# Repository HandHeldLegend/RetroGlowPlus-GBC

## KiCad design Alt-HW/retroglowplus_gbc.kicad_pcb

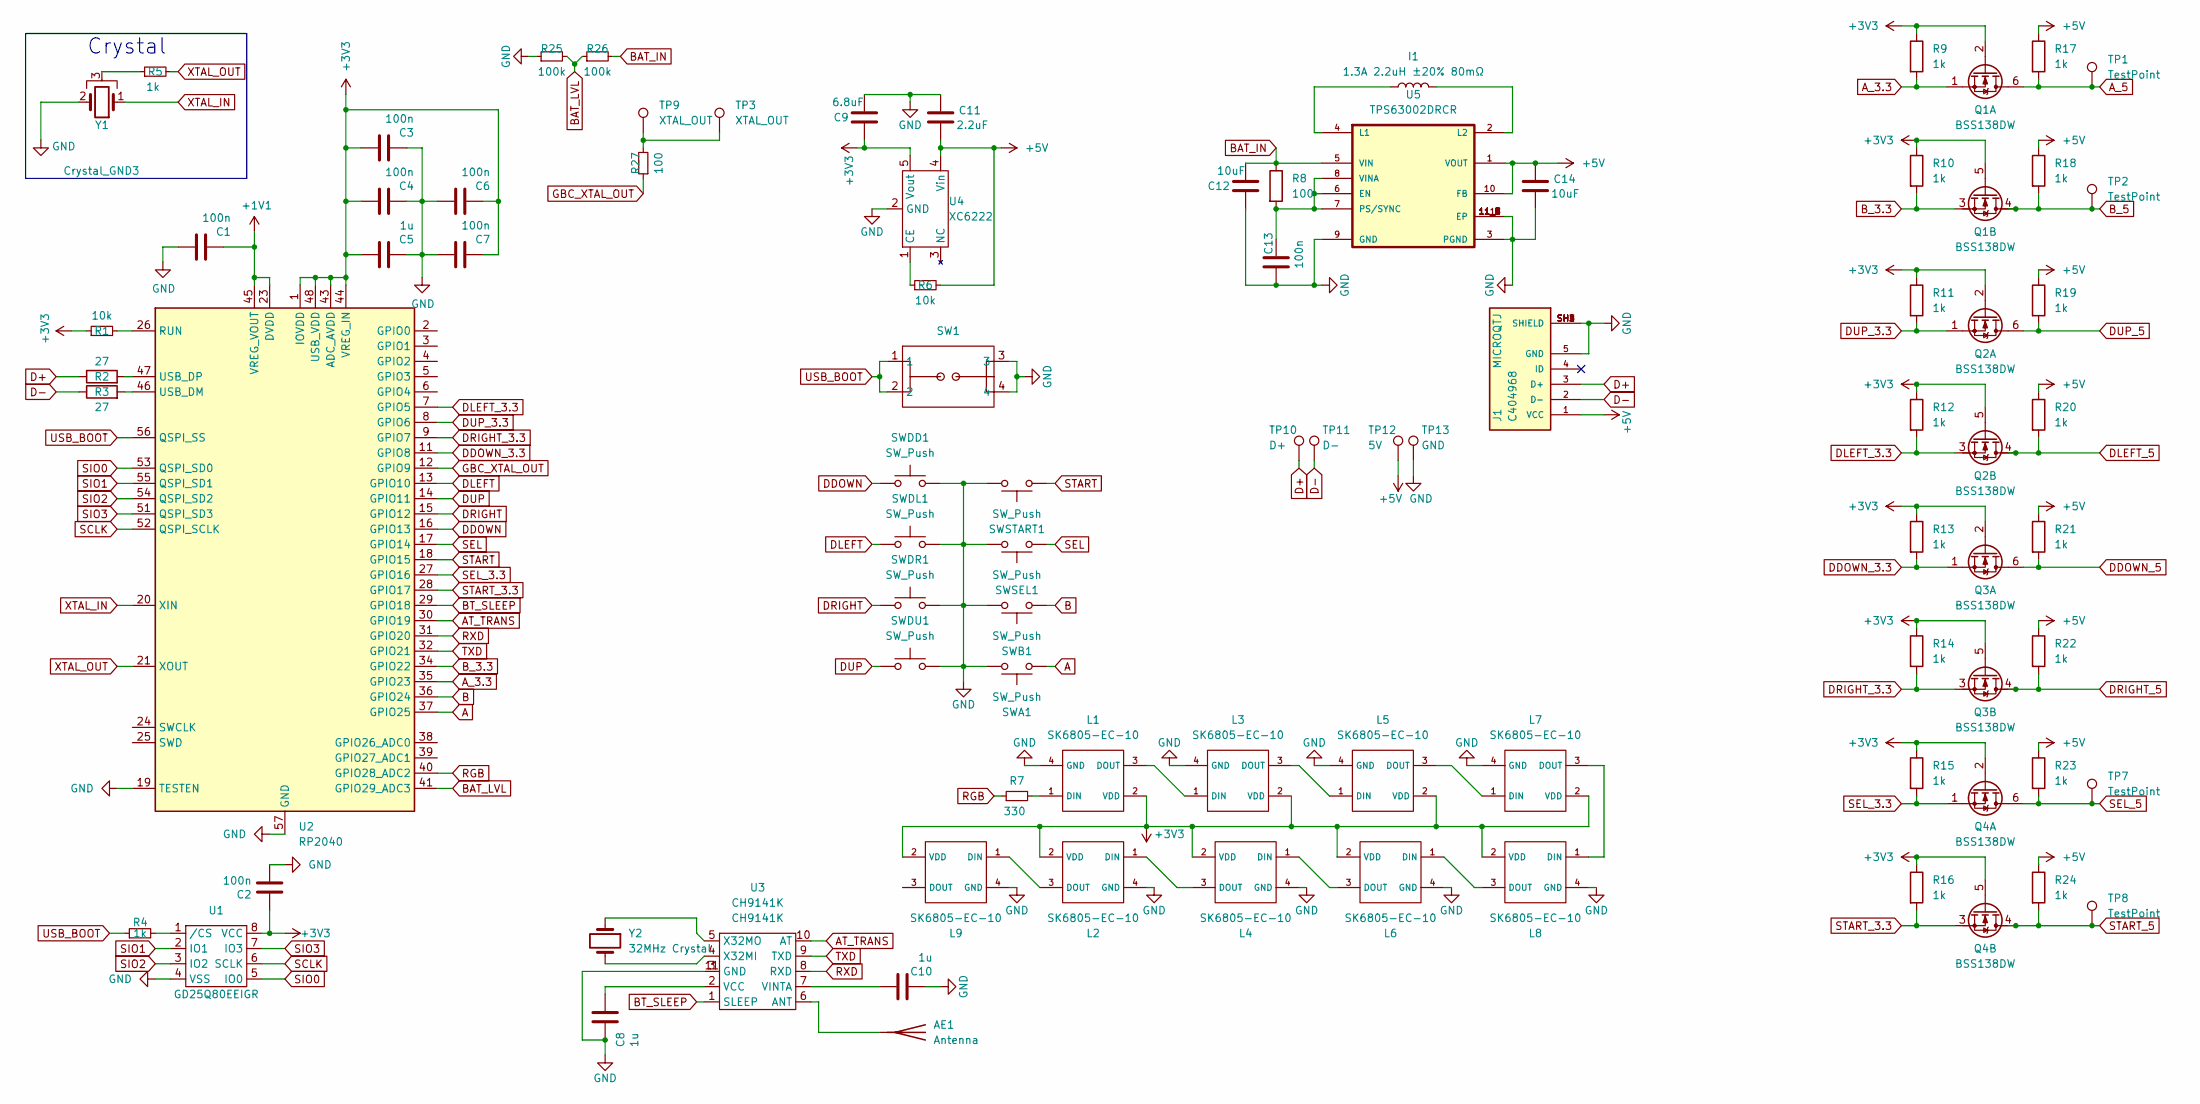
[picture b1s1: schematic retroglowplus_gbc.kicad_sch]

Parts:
AE1: Antenna; L_1206_3216Metric; MPN 2450AT18A100E
C1, C3, C4, C6, C7: 100n; C_0402_1005Metric
C2, C13: 100n; C_0201_0603Metric
C5, C8, C10: 1u; C_0402_1005Metric
C9: 6.8uF; C_0603_1608Metric
C11: 2.2uF; C_0603_1608Metric
C12, C14: 10uF; C_0805_2012Metric
I1: 1.3A 2.2uH ±20% 80mΩ; L_1008_2520Metric; MPN MIP25202R2MBE; LCSC C315721
J1: MICROQTJ; SHOUHAN_MICROQTJ; PARTREV A/0; LCSC C404968
L1, L2, L3, L4, L5, L6, L7, L8, L9: SK6805-EC-10
Q1, Q2, Q3, Q4: BSS138DW; SOT-363_SC-70-6; MPN BSS138DW-7-F; LCSC C154900
R1, R6: 10k; R_0201_0603Metric
R2, R3: 27; R_0201_0603Metric
R4, R5, R9, R10, R11, R12, R13, R14, R15, R16, R17, R18, R19, R20, R21, R22, R23, R24: 1k; R_0201_0603Metric
R7: 330; R_0201_0603Metric
R8, R27: 100; R_0201_0603Metric
R25, R26: 100k; R_0201_0603Metric
SW1: 1TS026A-1000-0550; MPN 1TS026A-1000-0550; LCSC C913778
SWA1: SW_Push; ring_pad_small
SWB1: SW_Push; ring_pad_small
SWDD1: SW_Push; ring_dpad
SWDL1: SW_Push; ring_dpad
SWDR1: SW_Push; ring_dpad
SWDU1: SW_Push; ring_dpad
SWSEL1: SW_Push; GBC_Start_Select
SWSTART1: SW_Push; GBC_Start_Select
TP1, TP2, TP7, TP8: TestPoint; TestPoint_Pad_2.5x2.5mm
TP3, TP9: XTAL_OUT; TestPoint_Pad_2.5x2.5mm
TP10: D+; TestPoint_Pad_2.5x2.5mm
TP11: D-; TestPoint_Pad_2.5x2.5mm
TP12: 5V; TestPoint_Pad_2.5x2.5mm
TP13: GND; TestPoint_Pad_2.5x2.5mm
U1: GD25Q80EEIGR; USON-8-EP(2x3); MPN GD25Q80EEIGR; LCSC C2874937
U2: RP2040; QFN-56-1EP_7x7mm_P0.4mm_EP3.2x3.2mm
U3: CH9141K; ESSOP-10; MPN CH9141K
U4: XC6222; SOT-89-5; MPN XC6222B331PR-G
U5: TPS63002DRCR; VREG_V62_16624-01YE; MPN TPS63002DRCR
Y1: Crystal_GND3; Resonator_SMD_Murata_CSTxExxV-3Pin_3.0x1.1mm; MPN CSTNE12M0GH5L000R0
Y2: 32MHz Crystal; Oscillator_SMD_EuroQuartz_XO32-4Pin_3.2x2.5mm; MPN CF4032M00012T5074007

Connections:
+1V1: C1.2, U2.23 (DVDD), U2.45 (VREG_VOUT), U2.50 (DVDD)
+3V3: C2.1, C3.1, C4.1, C5.1, C6.2, C7.2, C9.1, L1.2 (VDD), L2.2 (VDD), L3.2 (VDD), L4.2 (VDD), L5.2 (VDD), L6.2 (VDD), L7.2 (VDD), L8.2 (VDD), L9.2 (VDD), Q1.2 (G1), Q1.5 (G2), Q2.2 (G1), Q2.5 (G2), Q3.2 (G1), Q3.5 (G2), Q4.2 (G1), Q4.5 (G2), R1.1, R9.1, R10.1, R11.1, R12.1, R13.1, R14.1, R15.1, R16.1, U1.8 (VCC), U2.1 (IOVDD), U2.10 (IOVDD), U2.22 (IOVDD), U2.33 (IOVDD), U2.42 (IOVDD), U2.43 (ADC_AVDD), U2.44 (VREG_IN), U2.48 (USB_VDD), U2.49 (IOVDD), U4.5 (Vout)
+5V: C11.2, C14.1, J1.1 (VCC), R6.2, R17.1, R18.1, R19.1, R20.1, R21.1, R22.1, R23.1, R24.1, TP12.1, U4.4 (Vin), U5.1 (VOUT), U5.10 (FB); also elsewhere on the board
A: SWA1.1, U2.37 (GPIO25)
AT_TRANS: U2.30 (GPIO19), U3.10 (AT)
A_3.3: Q1.1 (S1), R9.2, U2.35 (GPIO23)
A_5: Q1.6 (D1), R17.2, TP1.1
B: SWB1.1, U2.36 (GPIO24)
BAT_IN: C12.2, R8.1, R26.2, U5.5 (VIN); also elsewhere on the board
BAT_LVL: R25.2, R26.1, U2.41 (GPIO29_ADC3)
BT_SLEEP: U2.29 (GPIO18), U3.1 (SLEEP)
B_3.3: Q1.3 (D2), R10.2, U2.34 (GPIO22)
B_5: Q1.4 (S2), R18.2, TP2.1
D+: J1.3 (D+), R2.1, TP10.1
D-: J1.2 (D-), R3.1, TP11.1
DDOWN: SWDD1.1, U2.16 (GPIO13)
DDOWN_3.3: Q3.1 (S1), R13.2, U2.11 (GPIO8)
DDOWN_5: Q3.6 (D1), R21.2
DLEFT: SWDL1.1, U2.13 (GPIO10)
DLEFT_3.3: Q2.3 (D2), R12.2, U2.7 (GPIO5)
DLEFT_5: Q2.4 (S2), R20.2
DRIGHT: SWDR1.1, U2.15 (GPIO12)
DRIGHT_3.3: Q3.3 (D2), R14.2, U2.9 (GPIO7)
DRIGHT_5: Q3.4 (S2), R22.2
DUP: SWDU1.1, U2.14 (GPIO11)
DUP_3.3: Q2.1 (S1), R11.2, U2.8 (GPIO6)
DUP_5: Q2.6 (D1), R19.2
GBC_XTAL_OUT: R27.1, U2.12 (GPIO9)
GND: C1.1, C2.2, C3.2, C4.2, C5.2, C6.1, C7.1, C8.2, C9.2, C10.2, C11.1, C12.1, C13.1, C14.2, J1.5 (GND), J1.SH1 (SHIELD), J1.SH2 (SHIELD), J1.SH3 (SHIELD), J1.SH4 (SHIELD), L1.4 (GND), L2.4 (GND), L3.4 (GND), L4.4 (GND), L5.4 (GND), L6.4 (GND), L7.4 (GND), L8.4 (GND), L9.4 (GND), R25.1, SW1.3, SW1.4, SWA1.2, SWB1.2, SWDD1.2, SWDL1.2, SWDR1.2, SWDU1.2, SWSEL1.2, SWSTART1.2, TP13.1, U1.4 (VSS), U2.19 (TESTEN), U2.57 (GND), U3.3 (GND), U3.11 (GND), U4.2 (GND), U5.3 (PGND), U5.9 (GND), U5.11 (EP), U5.11_1 (EP), U5.11_2 (EP), U5.11_3 (EP), U5.11_4 (EP), U5.11_5 (EP), U5.11_6 (EP), U5.11_7 (EP), U5.11_8 (EP), Y1.2; also elsewhere on the board
unnamed: AE1.1 (A), U3.6 (ANT)
unnamed: L1.1 (DIN), R7.2
unnamed: L1.3 (DOUT), L3.1 (DIN)
unnamed: L2.1 (DIN), L4.3 (DOUT)
unnamed: L2.3 (DOUT), L9.1 (DIN)
unnamed: L3.3 (DOUT), L5.1 (DIN)
unnamed: L4.1 (DIN), L6.3 (DOUT)
unnamed: L5.3 (DOUT), L7.1 (DIN)
unnamed: L6.1 (DIN), L8.3 (DOUT)
unnamed: L7.3 (DOUT), L8.1 (DIN)
unnamed: R5.1, Y1.3
unnamed: R27.2, TP3.1, TP9.1
unnamed: R4.2, U1.1 (/CS)
unnamed: R1.2, U2.26 (RUN)
unnamed: R3.2, U2.46 (USB_DM)
unnamed: R2.2, U2.47 (USB_DP)
unnamed: C8.1, U3.2 (VCC)
unnamed: C10.1, U3.7 (VINTA)
unnamed: U3.4 (X32MI), Y2.2
unnamed: U3.5 (X32MO), Y2.1
unnamed: R6.1, U4.1 (CE)
unnamed: C13.2, R8.2, U5.6 (EN), U5.7 (PS/SYNC), U5.8 (VINA)
unnamed: I1.1, U5.4 (L1)
unnamed: I1.2, U5.2 (L2)
RGB: R7.1, U2.40 (GPIO28_ADC2)
RXD: U2.31 (GPIO20), U3.8 (RXD)
SCLK: U1.6 (SCLK), U2.52 (QSPI_SCLK)
SEL: SWSEL1.1, U2.17 (GPIO14)
SEL_3.3: Q4.1 (S1), R15.2, U2.27 (GPIO16)
SEL_5: Q4.6 (D1), R23.2, TP7.1
SIO0: U1.5 (IO0), U2.53 (QSPI_SD0)
SIO1: U1.2 (IO1), U2.55 (QSPI_SD1)
SIO2: U1.3 (IO2), U2.54 (QSPI_SD2)
SIO3: U1.7 (IO3), U2.51 (QSPI_SD3)
START: SWSTART1.1, U2.18 (GPIO15)
START_3.3: Q4.3 (D2), R16.2, U2.28 (GPIO17)
START_5: Q4.4 (S2), R24.2, TP8.1
TXD: U2.32 (GPIO21), U3.9 (TXD)
USB_BOOT: R4.1, SW1.1, SW1.2, U2.56 (QSPI_SS)
XTAL_IN: U2.20 (XIN), Y1.1
XTAL_OUT: R5.2, U2.21 (XOUT)

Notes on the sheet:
Crystal

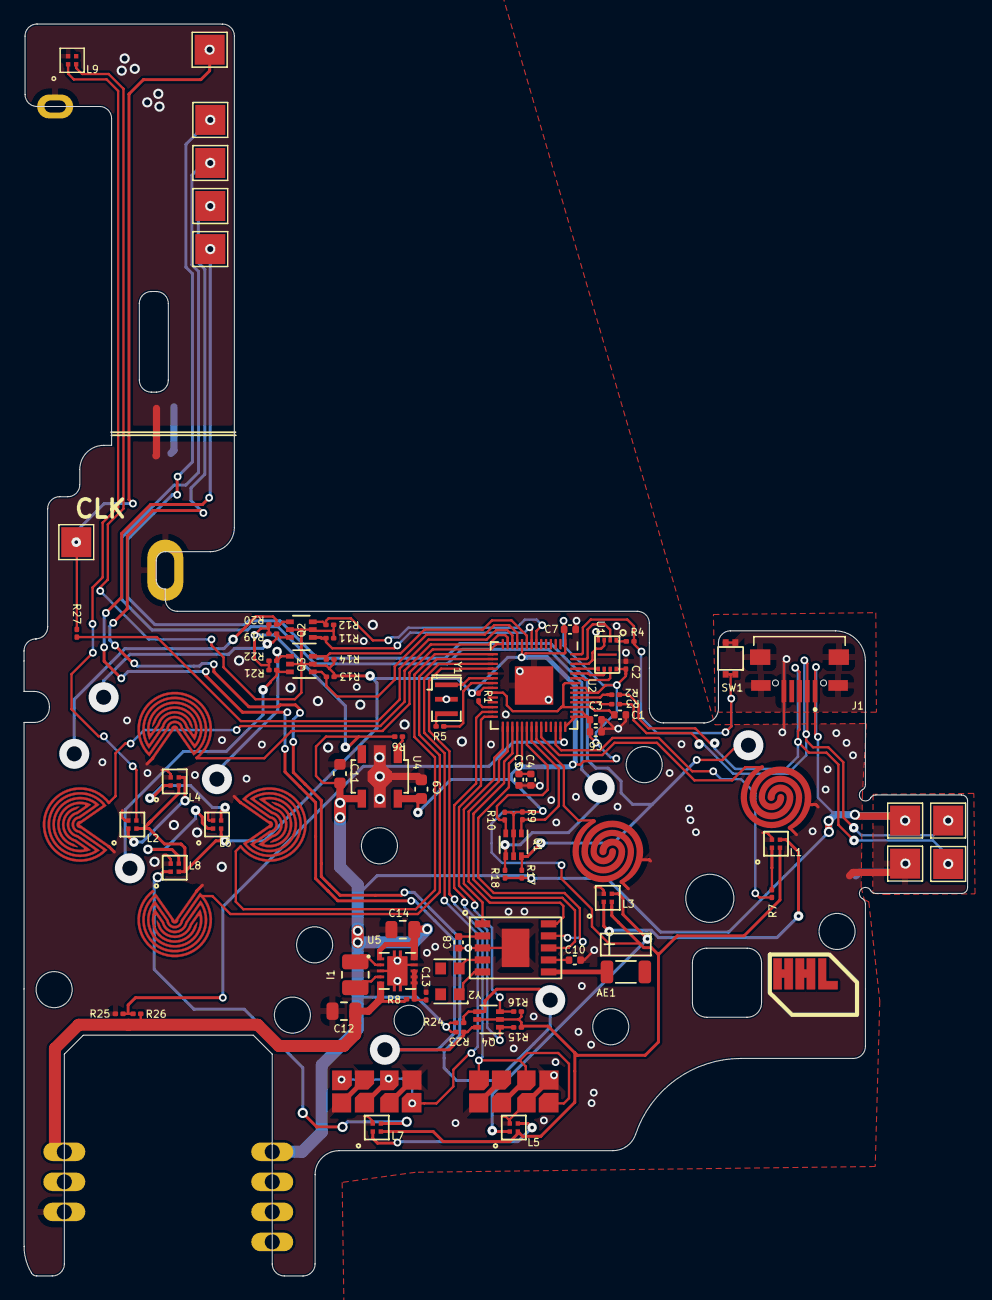
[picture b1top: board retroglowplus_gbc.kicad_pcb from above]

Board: 2 copper layers, 78.5 x 104.2 mm, 93 parts (0 on the bottom side), 70 nets.

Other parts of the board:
BAT1: TestPoint_Plated_Hole_D2.0mm
G1, G2, G3: TestPoint_Plated_Hole_D2.0mm
LOGO: HHL_Logo
NC1, NC2, NC3, NC4: TestPoint_Plated_Hole_D2.0mm
VOUT1: TestPoint_Plated_Hole_D2.0mm

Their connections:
+5V: VOUT1.1; also elsewhere on the board
BAT_IN: BAT1.1; also elsewhere on the board
GND: G1.1, G2.1, G3.1; also elsewhere on the board

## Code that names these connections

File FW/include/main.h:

#include "hoja_includes.h"

#define GPIO_DLEFT_3    5
#define GPIO_DUP_3      6
#define GPIO_DRIGHT_3   7
#define GPIO_DDOWN_3    8
#define GPIO_DLEFT      10
#define GPIO_DUP        11
#define GPIO_DRIGHT     12
#define GPIO_DDOWN      13
#define GPIO_SELECT     14
#define GPIO_START      15
#define GPIO_SELECT_3   16
#define GPIO_START_3    17
#define GPIO_BT_SLEEP   18
#define GPIO_AT_TRANS   19
#define GPIO_RXD        20
#define GPIO_TXD        21
#define GPIO_B_3        22
#define GPIO_A_3        23
#define GPIO_B          24
#define GPIO_A          25
#define GPIO_BAT_LEVEL  29
#define ADC_BAT_LEVEL   3

  

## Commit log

2024-04-02 Add 2 layer
2024-04-03 Add gerbers
